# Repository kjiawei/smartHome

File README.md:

简书:jkCodic
链接:https://www.jianshu.com/u/b28b2d73e999

### smartHome 智能家居-智慧应用
#### 控制端软件(包括服务端 客户端 开发板) intelligent home controller
#### python等实现的信息获取 信息处理 咨询查询 微信好友处理的脚本操作

欢迎关注我的公众号
【喵叫瘦星人】

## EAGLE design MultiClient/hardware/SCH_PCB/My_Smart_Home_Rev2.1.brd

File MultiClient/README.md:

# 目录结构说明

***

## server

服务器端程序(主要在Ubuntu12.04上测试, linux平台编译，运行都是没问题的)

使用方法请参考[编译和安装](http://git.oschina.net/xmeter/My-smart-home/wikis/%E7%BC%96%E8%AF%91%E5%92%8C%E5%AE%89%E8%A3%85)

友情提示go语言服务器版本请移步

http://git.oschina.net/ckrissun/smarthome-server

## dserver
 下一版开发的重点，服务器端由集中式变为分布式架构。
 
## tools 

提供些由于网络问题不好或者政策原因，软件包及调试工具

## opencv/facedect

人脸检测的源代码及例子(基于opencv + haar)

##  FastDFS

提供分布式云存储服务 ，感谢 Happy Fish / YuQing 的辛勤劳动

更多详细信息：http://www.csource.org/ 或者 googlecode有此项目

## iOS_Client、Android_Client、FirefoxOS_Client

各平台的客户端

* iOS客户端使用xcode5或以上打开即可

* Andriod客户端使用eclipse打开即可

 假如没有android开发环境， 可直接下载[已编译的Apk](http://git.oschina.net/xmeter/My-smart-home/blob/Client/Android_Client/bin/MyNode.apk)

* FirefoxOS客户端使用除记事本外的文本编辑器打开即可

**PS:现在客户端相关移至Client分支，确认无误后合并至master**

## ClientAPI、ClientWeb、ServerAPI、ServerWeb

http服务器代码，有问题请[提交Issue](http://git.oschina.net/xmeter/My-smart-home/issues/new)

**PS:现在Web相关移至Server分支，确认无误后合并至master**

## webhook

代码自动部署，持续集成

## hardware

硬件ardunio以及相关传感器的demo。(LM35，MQ2 MQ7 , W5100等)
     
* [硬件介绍](http://git.oschina.net/xmeter/My-smart-home/wikis/%E7%A1%AC%E4%BB%B6%E9%83%A8%E5%88%86%E4%BB%8B%E7%BB%8D)
       
***

> 更详细的说明，请移步 [WiKi](http://git.oschina.net/xmeter/My-smart-home/wikis/Home)

> 希望有新的小伙伴加入！

# 联系方式

***

### [李子](git.oschina.net/xmeter) liyongming1982@163.com _管理员_

服务器、硬件、Android Client

### [Rex](http://git.oschina.net/ckrissun) ckrissun@gmail.com _管理员_

服务器、协议、硬件

### [泷涯](http://git.oschina.net/sy) 896640547@qq.com _管理员_

数据库、Web、API
 
### [Pajoke](http://git.oschina.net/hell-prototypes) pajoke@163.com

硬件

更多Pajoke介绍请移步 ：  http://www.hellprototypes.com

### [siz](http://git.oschina.net/aliyuns) siz@sonwa.cn

iOS Client

### [fireman](http://git.oschina.net/colma) david_lxh@aliyun.com

特别感谢fireman，把Web服务移植到树莓派 (并写下文档供后来者参考)

### [Raythan](http://git.oschina.net/Raythan) raythandong@gmail.com

硬件

### [孤鹰](http://git.oschina.net/604217454) 604217454@qq.com

iOS Client

### [mzer](http://git.oschina.net/liduanjun) liduanjun@126.com

硬件及Web

# 感谢

***

   * 感谢xiangjm资助我200元人民币购买3D打印机
   * 感谢我老婆这个月多给了我点零花钱
   * 感谢3D淘宝店老板便宜了50元钱 http://3dprinter-diy.taobao.com/?spm=2013.1.0.0.donECP
   * ......

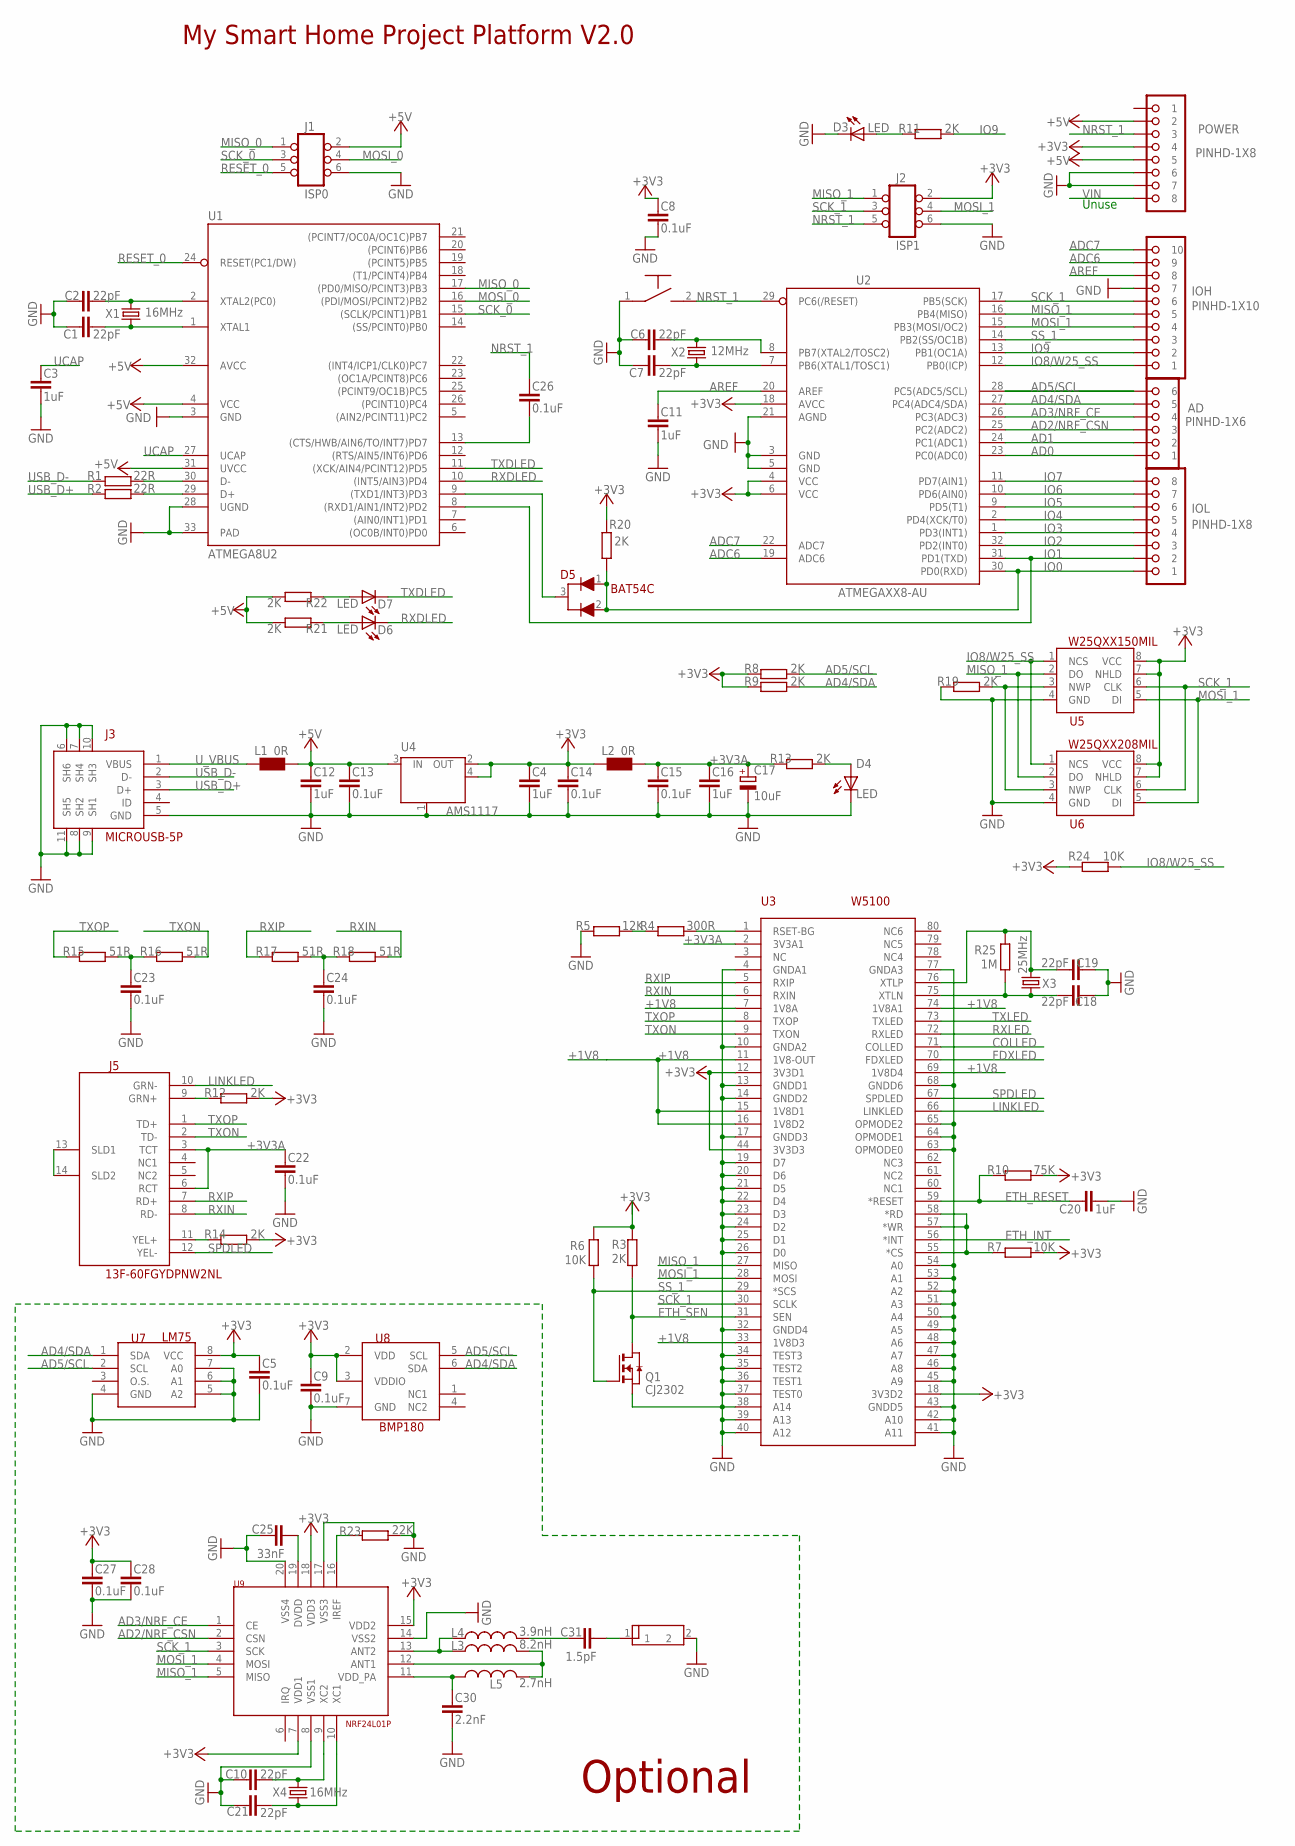
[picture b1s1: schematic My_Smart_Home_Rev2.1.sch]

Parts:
AD: PINHD-1X6; 1X06
ANT1: 2.4G_ANT1; 2.4G_PCB_ANT
C1, C2, C6, C7, C10, C18, C19, C21: 22pF; C0603
C3, C4, C11, C12, C16, C20: 1uF; C0603
C5, C8, C9, C13, C14, C15, C22, C23, C24, C26, C27, C28: 0.1uF; C0603
C17: 10uF; C0805
C25: 33nF; C0603
C30: 2.2nF; C0603
C31: 1.5pF; C0603
D3, D4, D6, D7: LED; LED0805
D5: BAT54C; SOT23
IOH: PINHD-1X10; 1X10
IOL: PINHD-1X8; 1X08
J1: ISP0; 2X03
J2: ISP1; 2X03
J3: MICROUSB-5P; MICROUSB-5P-SMD
J5: 13F-60FGYDPNW2NL
L1, L2: 0R; R0603
L3: 8.2nH; R0603
L4: 3.9nH; R0603
L5: 2.7nH; R0603
POWER: PINHD-1X8; 1X08
Q1: CJ2302; SOT23
R1, R2: 22R; R0603
R3, R8, R9, R11, R12, R13, R14, R19, R20, R21, R22: 2K; R0603
R4: 300R; R0603
R5: 12K; R0603
R6, R7, R24: 10K; R0603
R10: 75K; R0603
R15, R16, R17, R18: 51R; R0603
R23: 22K; R0603
R25: 1M; R0603
SW2: SW-2; SW-2P-SMD
U1: ATMEGA8U2; MLF32
U2: ATMEGAXX8-AU; TQFP32-08
U3: W5100; SQFP-S-10X10-80
U4: AMS1117; SOT223
U5: W25QXX150MIL; 8S1
U6: W25QXX208MIL; 8S2
U7: LM75; 8S1
U8: BMP180; LGA-7P
U9: NRF24L01P; QFN20
X1, X4: 16MHz; HC49UP
X2: 12MHz; HC49UP
X3: 25MHz; HC49UP

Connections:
+1V8: U3.7 (1V8A), U3.11 (1V8-OUT), U3.15 (1V8D1), U3.16 (1V8D2), U3.33 (1V8D3), U3.69 (1V8D4), U3.74 (1V8A1)
+3V3: C4.2, C5.2, C8.2, C9.2, C14.2, C27.2, C28.2, J2.2, L2.1, POWER.4, R3.2, R6.1, R7.2, R8.2, R9.2, R10.2, R12.1, R14.1, R20.2, R24.1, U2.4 (VCC), U2.6 (VCC), U2.18 (AVCC), U3.12 (3V3D1), U3.18 (3V3D2), U3.44 (3V3D3), U4.2 (OUT), U4.4 (OUT), U5.7 (NHLD), U5.8 (VCC), U6.7 (NHLD), U6.8 (VCC), U7.8 (VCC), U8.2 (VDD), U8.3 (VDDIO), U9.7 (VDD1), U9.15 (VDD2), U9.18 (VDD3)
+3V3A: C15.2, C16.2, C17.1 (+), C22.2, J5.3 (TCT), J5.6 (RCT), L2.2, R13.2, U3.2 (3V3A1)
+5V: C12.2, C13.2, J1.2, L1.2, POWER.2, POWER.5, R21.1, R22.1, U1.4 (VCC), U1.31 (UVCC), U1.32 (AVCC), U4.3 (IN)
AD0: AD.1, U2.23 (PC0(ADC0))
AD1: AD.2, U2.24 (PC1(ADC1))
AD2/NRF_CSN: AD.3, U2.25 (PC2(ADC2)), U9.2 (CSN)
AD3/NRF_CE: AD.4, U2.26 (PC3(ADC3)), U9.1 (CE)
AD4/SDA: AD.5, R9.1, U2.27 (PC4(ADC4/SDA)), U7.1 (SDA), U8.6 (SDA)
AD5/SCL: AD.6, R8.1, U2.28 (PC5(ADC5/SCL)), U7.2 (SCL), U8.5 (SCL)
ADC6: IOH.9, U2.19 (ADC6)
ADC7: IOH.10, U2.22 (ADC7)
AREF: C11.2, IOH.8, U2.20 (AREF)
COLLED: U3.71 (COLLED)
ETH_INT: U3.56 (*INT)
ETH_RESET: C20.2, R10.1, U3.59 (*RESET)
ETH_SEN: Q1.3 (D), R3.1, U3.31 (SEN)
FDXLED: U3.70 (FDXLED)
GND: ANT1.2, C1.1, C2.1, C3.1, C4.1, C5.1, C6.1, C7.1, C8.1, C9.1, C10.1, C11.1, C12.1, C13.1, C14.1, C15.1, C16.1, C17.2 (-), C18.1, C19.1, C20.1, C21.1, C22.1, C23.1, C24.1, C25.2, C27.1, C28.1, C30.1, D3.C, D4.C, IOH.7, J1.6, J2.6, J3.5 (GND), J3.6 (SH6), J3.7 (SH4), J3.8 (SH2), J3.9 (SH1), J3.10 (SH3), J3.11 (SH5), POWER.6, POWER.7, Q1.2 (S), R5.1, R19.2, R23.1, SW2.1, U1.3 (GND), U1.28 (UGND), U1.33 (PAD), U2.3 (GND), U2.5 (GND), U2.21 (AGND), U3.4 (GNDA1), U3.10 (GNDA2), U3.13 (GNDD1), U3.14 (GNDD2), U3.17 (GNDD3), U3.19 (D7), U3.20 (D6), U3.21 (D5), U3.22 (D4), U3.23 (D3), U3.24 (D2), U3.25 (D1), U3.26 (D0), U3.32 (GNDD4), U3.34 (TEST3), U3.35 (TEST2), U3.36 (TEST1), U3.37 (TEST0), U3.38 (A14), U3.39 (A13), U3.40 (A12), U3.41 (A11), U3.42 (A10), U3.43 (GNDD5), U3.45 (A9), U3.46 (A8), U3.47 (A7), U3.48 (A6), U3.49 (A5), U3.50 (A4), U3.51 (A3), U3.52 (A2), U3.53 (A1), U3.54 (A0), U3.63 (OPMODE0), U3.64 (OPMODE1), U3.65 (OPMODE2), U3.68 (GNDD6), U3.77 (GNDA3), U4.1 (GND/ADJ), U5.4 (GND), U6.4 (GND), U7.4 (GND), U7.5 (A2), U7.6 (A1), U7.7 (A0), U8.7 (GND), U9.8 (VSS1), U9.14 (VSS2), U9.17 (VSS3), U9.20 (VSS4)
IO0: D5.1, D5.2, IOL.1, R20.1, U2.30 (PD0(RXD))
IO1: IOL.2, U1.8 ((RXD1/AIN1/INT2)PD2), U2.31 (PD1(TXD))
IO2: IOL.3, U2.32 (PD2(INT0))
IO3: IOL.4, U2.1 (PD3(INT1))
IO4: IOL.5, U2.2 (PD4(XCK/T0))
IO5: IOL.6, U2.9 (PD5(T1))
IO6: IOL.7, U2.10 (PD6(AIN0))
IO7: IOL.8, U2.11 (PD7(AIN1))
IO8/W25_SS: IOH.1, R24.2, U2.12 (PB0(ICP)), U5.1 (NCS), U6.1 (NCS)
IO9: IOH.2, R11.1, U2.13 (PB1(OC1A))
LINKLED: J5.10 (GRN-), U3.66 (LINKLED)
MISO_0: J1.1, U1.17 ((PD0/MISO/PCINT3)PB3)
MISO_1: IOH.5, J2.1, U2.16 (PB4(MISO)), U3.27 (MISO), U5.2 (DO), U6.2 (DO), U9.5 (MISO)
MOSI_0: J1.4, U1.16 ((PDI/MOSI/PCINT2)PB2)
MOSI_1: IOH.4, J2.4, U2.15 (PB3(MOSI/OC2)), U3.28 (MOSI), U5.5 (DI), U6.5 (DI), U9.4 (MOSI)
unnamed: C2.2, U1.2 (XTAL2(PC0)), X1.2
unnamed: C1.2, U1.1 (XTAL1), X1.1
unnamed: C18.2, R25.2, U3.75 (XTLN), X3.2
unnamed: R7.1, U3.55 (*CS), U3.57 (*WR), U3.58 (*RD)
unnamed: C19.2, R25.1, U3.76 (XTLP), X3.1
unnamed: C10.2, U9.9 (XC2), X4.2
unnamed: D5.3, U1.9 ((TXD1/INT3)PD3)
unnamed: C26.1, U1.13 ((CTS/HWB/AIN6/TO/INT7)PD7)
unnamed: R1.2, U1.30 (D-)
unnamed: D7.A, R22.2
unnamed: R2.2, U1.29 (D+)
unnamed: C21.2, U9.10 (XC1), X4.1
unnamed: L3.1, L4.1, U9.13 (ANT2)
unnamed: D4.A, R13.1
unnamed: D3.A, R11.2
unnamed: C6.2, U2.8 (PB7(XTAL2/TOSC2)), X2.2
unnamed: C7.2, U2.7 (PB6(XTAL1/TOSC1)), X2.1
unnamed: R4.2, U3.1 (RSET-BG)
unnamed: R4.1, R5.2
unnamed: J5.11 (YEL+), R14.2
unnamed: J5.9 (GRN+), R12.2
unnamed: C23.2, R15.1, R16.2
unnamed: D6.A, R21.2
unnamed: R23.2, U9.16 (IREF)
unnamed: J5.13 (SLD1), J5.14 (SLD2)
unnamed: C25.1, U9.19 (DVDD)
unnamed: C24.2, R17.1, R18.2
unnamed: L3.2, L5.2, U9.12 (ANT1)
unnamed: C30.2, L5.1, U9.11 (VDD_PA)
unnamed: R19.1, U5.3 (NWP), U6.3 (NWP)
unnamed: ANT1.1, C31.1
unnamed: C31.2, L4.2
NRST_1: C26.2, J2.5, POWER.3, SW2.2, U2.29 (PC6(/RESET))
RESET_0: J1.5, U1.24 (RESET(PC1/DW))
RXDLED: D6.C, U1.10 ((INT5/AIN3)PD4)
RXIN: J5.8 (RD-), R18.1, U3.6 (RXIN)
RXIP: J5.7 (RD+), R17.2, U3.5 (RXIP)
RXLED: U3.72 (RXLED)
SCK_0: J1.3, U1.15 ((SCLK/PCINT1)PB1)
SCK_1: IOH.6, J2.3, U2.17 (PB5(SCK)), U3.30 (SCLK), U5.6 (CLK), U6.6 (CLK), U9.3 (SCK)
SPDLED: J5.12 (YEL-), U3.67 (SPDLED)
SS_1: IOH.3, Q1.1 (G), R6.2, U2.14 (PB2(SS/OC1B)), U3.29 (*SCS)
TXDLED: D7.C, U1.11 ((XCK/AIN4/PCINT12)PD5)
TXLED: U3.73 (TXLED)
TXON: J5.2 (TD-), R16.1, U3.9 (TXON)
TXOP: J5.1 (TD+), R15.2, U3.8 (TXOP)
UCAP: C3.2, U1.27 (UCAP)
USB_D+: J3.3 (D+), R2.1
USB_D-: J3.2 (D-), R1.1
U_VBUS: J3.1 (VBUS), L1.1
VIN: POWER.8

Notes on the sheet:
Unuse
My Smart Home Project Platform V2.0
Optional

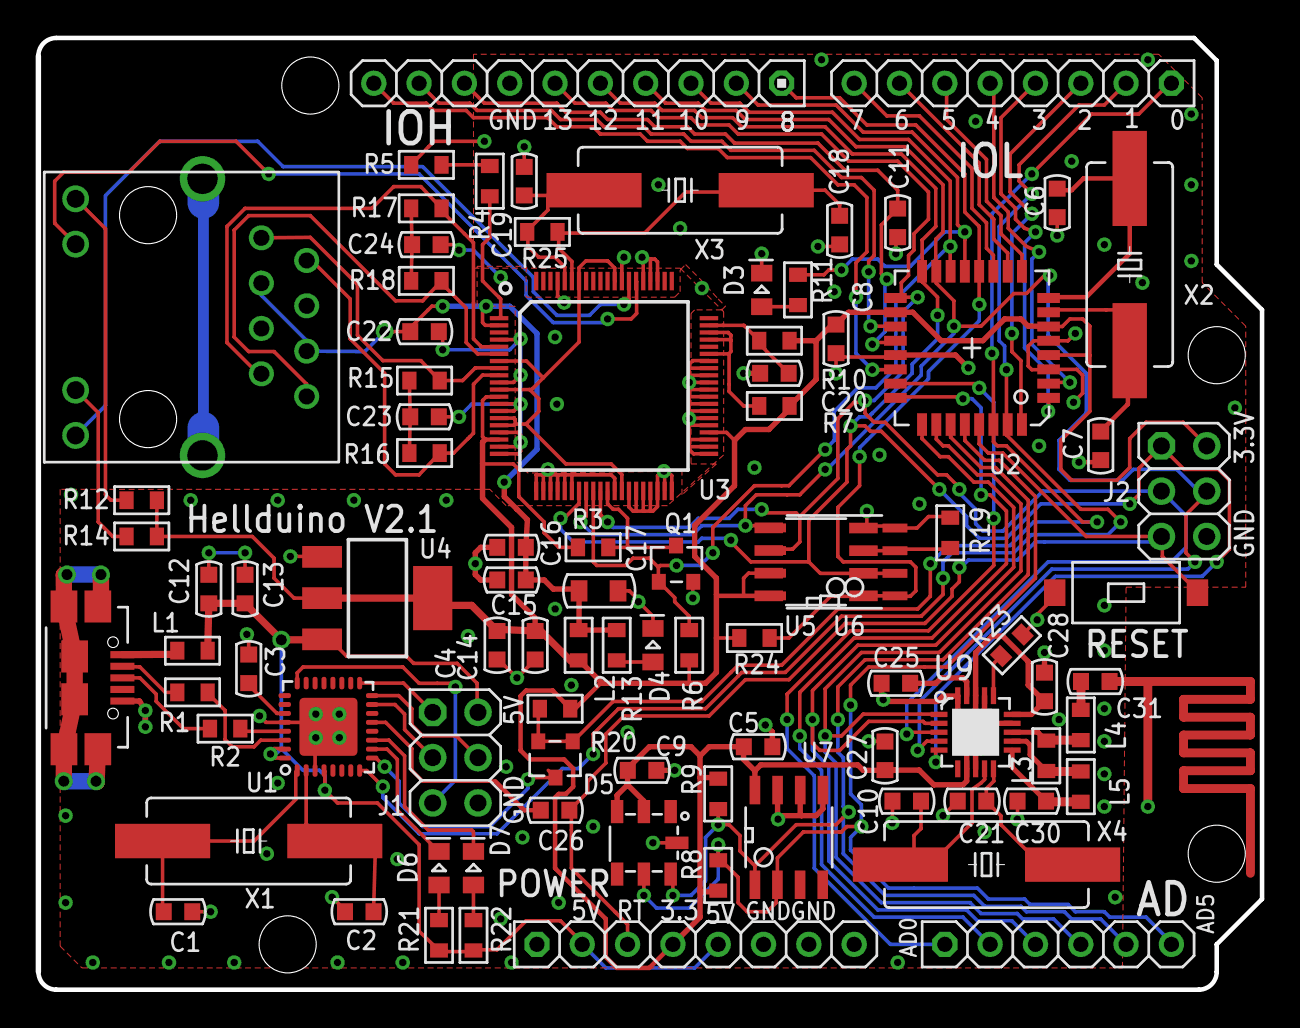
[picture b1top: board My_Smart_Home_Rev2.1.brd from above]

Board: 2 copper layers, 68.6 x 53.3 mm, 89 parts (0 on the bottom side), 79 nets.

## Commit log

2018-08-22 create py folder
    123
2018-08-22 music_download v0.0.1
2018-08-22 add some function declaritions
2018-08-22 some direction add
2018-12-07 添加保存数据库功能
2019-02-03 2019 new year change
    2019 new year change
2019-02-03 2
    2
2019-02-03 3
    3
2019-05-20 51Car
    stc89c52
2019-05-22 free project
    photo manage
2019-05-28 others project
    1
2019-05-28 php shop
    1
2019-05-28 note
    1
2019-11-21 1
    1
2020-10-26 Update auto_click.py
    chromedriver --version:84.0.4147.30 (48b3e868b4cc0aa7e8149519690b6f6949e110a8-refs/branch-heads/4147@{#310})
